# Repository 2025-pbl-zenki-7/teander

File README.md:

# teander

2025年度　前期　PBL 第７班　のレポジトリ

## ハード部分 Relay_Switch

以下回路図

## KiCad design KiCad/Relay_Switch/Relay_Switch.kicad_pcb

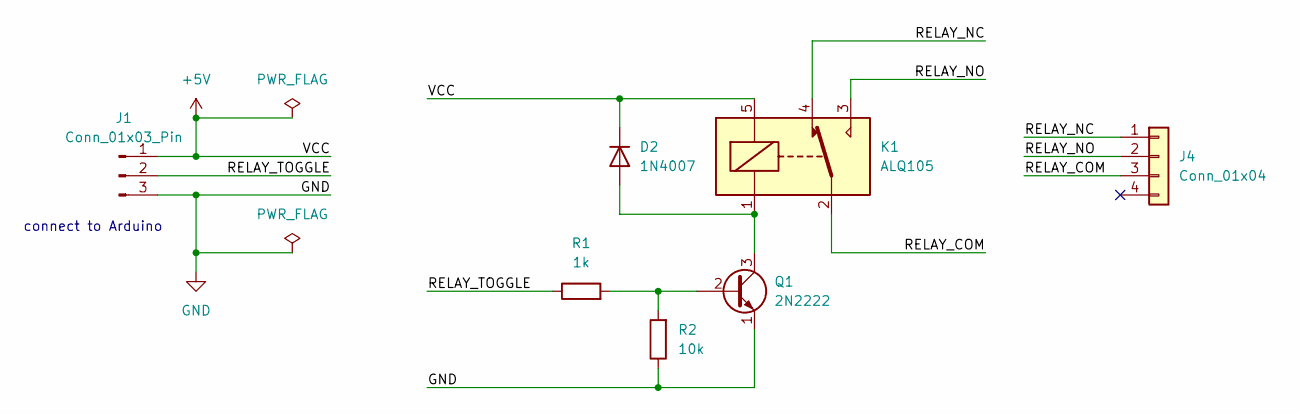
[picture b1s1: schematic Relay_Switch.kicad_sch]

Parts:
D2: 1N4007; D_DO-41_SOD81_P10.16mm_Horizontal
J1: Conn_01x03_Pin; PinHeader_1x03_P2.54mm_Vertical
J4: Conn_01x04; ML-250
K1: ALQ105; Relay_SPDT_Omron-G5Q-1
Q1: 2N2222; TO-92L_Inline_Wide
R1: 1k; R_Axial_DIN0207_L6.3mm_D2.5mm_P10.16mm_Horizontal
R2: 10k; R_Axial_DIN0207_L6.3mm_D2.5mm_P10.16mm_Horizontal

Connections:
+5V: D2.1 (K), J1.1, K1.5
/RELAY_COM: J4.3, K1.2
/RELAY_NC: J4.1, K1.4
/RELAY_NO: J4.2, K1.3
/RELAY_TOGGLE: J1.2, R1.1
GND: J1.3, Q1.1 (E), R2.1
unnamed: D2.2 (A), K1.1, Q1.3 (C)
unnamed: Q1.2 (B), R1.2, R2.2

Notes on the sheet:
connect to Arduino

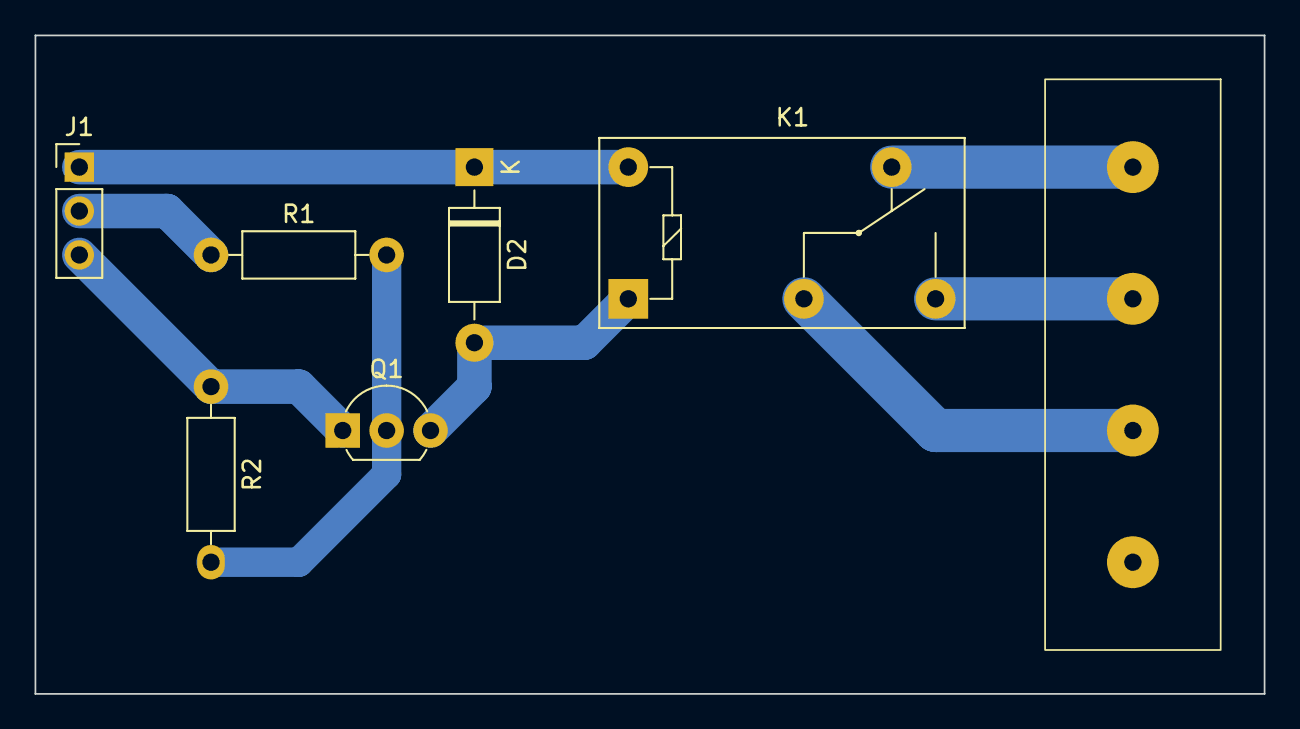
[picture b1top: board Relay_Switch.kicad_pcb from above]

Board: 2 copper layers, 71.1 x 38.1 mm, 7 parts (0 on the bottom side), 8 nets.

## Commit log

2025-06-06 add pbl.ino
2025-06-06 ds_store
2025-06-23 add .gitignore
2025-06-23 add Relay_Switch KiCad Project
2025-06-23 modified
2025-06-23 add Relay_Toggle_Test.ino
2025-06-27 add main.ino
2025-06-30 add images
2025-07-04 pio init
2025-07-07 rename pio/src/main.ino to main.cpp
2025-07-07 kankyo ikou simasita
2025-07-07 rm Arduino
2025-07-08 pio setup
2025-07-18 update gitignore
